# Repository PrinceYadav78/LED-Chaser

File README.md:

Designined in KiCAD, and FreeCAD

### Schematic

### PCB

### bom.csv

### Cart

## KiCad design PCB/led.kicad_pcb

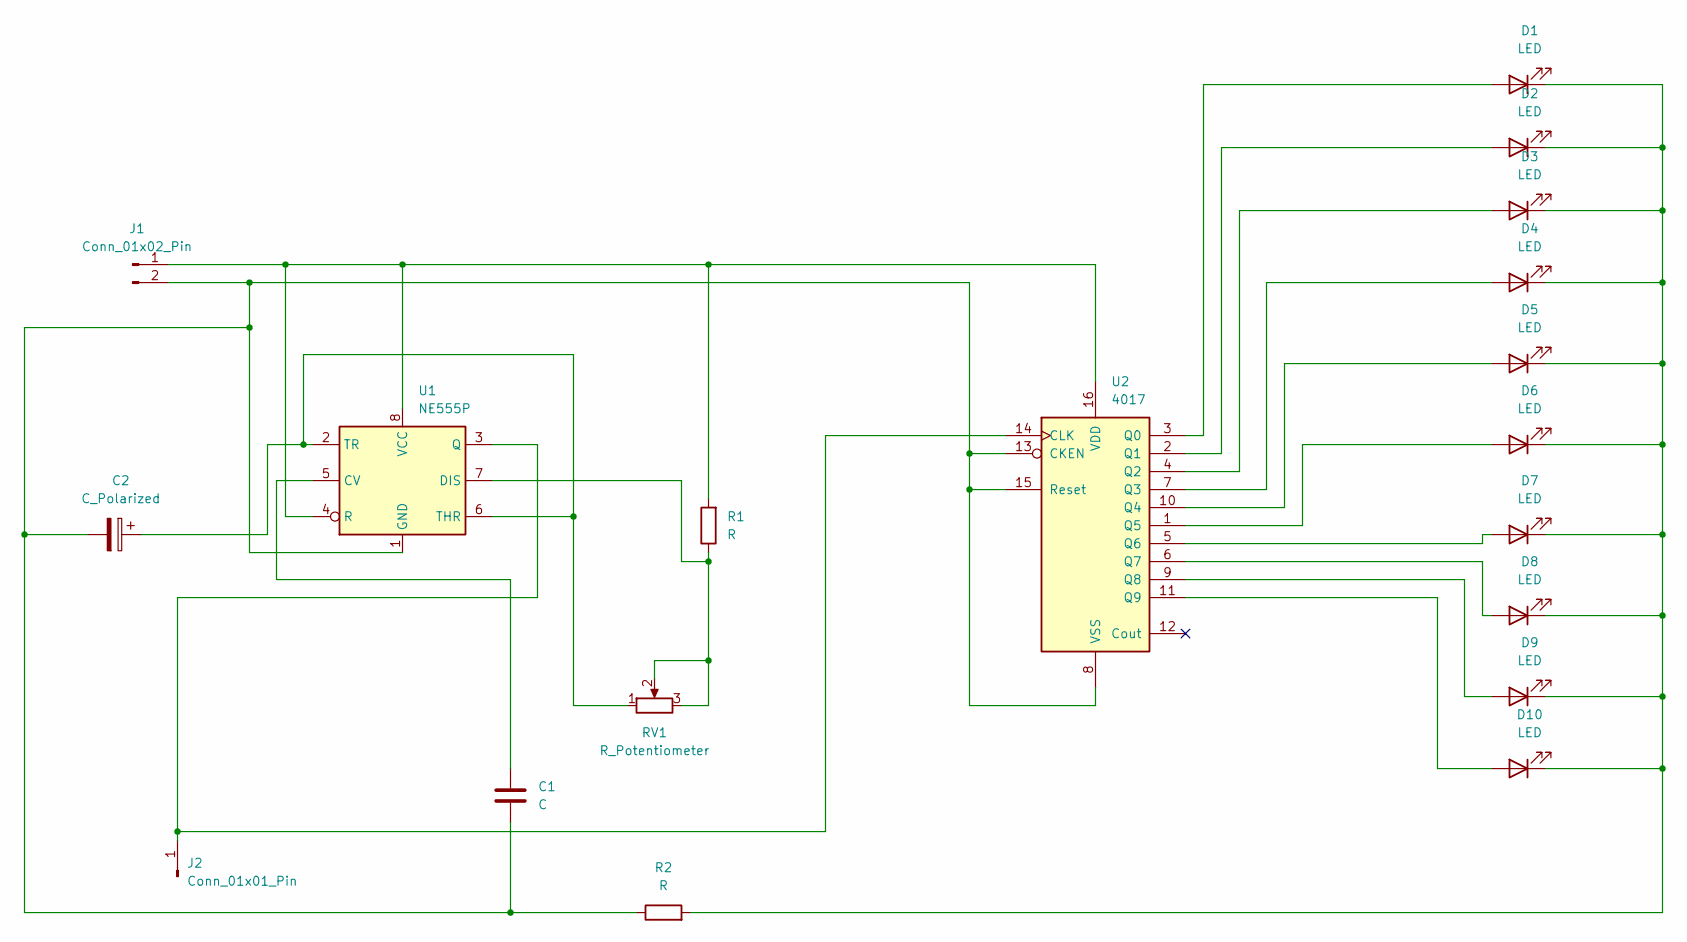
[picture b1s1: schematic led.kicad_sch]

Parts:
C1: C; C_Disc_D5.0mm_W2.5mm_P5.00mm
C2: C_Polarized; CP_Radial_D5.0mm_P2.50mm
D1, D2, D3, D4, D5, D6, D7, D8, D9, D10: LED; LED_D5.0mm
J1: Conn_01x02_Pin; PinHeader_1x02_P2.54mm_Vertical
J2: Conn_01x01_Pin; PinHeader_1x01_P2.54mm_Vertical
R1, R2: R; R_Axial_DIN0207_L6.3mm_D2.5mm_P7.62mm_Horizontal
RV1: R_Potentiometer; TRIM_3362P-1-103LF
U1: NE555P; DIP-8_W7.62mm
U2: 4017; DIP-16_W7.62mm

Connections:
unnamed: D1.2 (A), U2.3 (Q0)
unnamed: D1.1 (K), D2.1 (K), D3.1 (K), D4.1 (K), D5.1 (K), D6.1 (K), D7.1 (K), D8.1 (K), D9.1 (K), D10.1 (K), R2.2
unnamed: D2.2 (A), U2.2 (Q1)
unnamed: D3.2 (A), U2.4 (Q2)
unnamed: D4.2 (A), U2.7 (Q3)
unnamed: D5.2 (A), U2.10 (Q4)
unnamed: D6.2 (A), U2.1 (Q5)
unnamed: D7.2 (A), U2.5 (Q6)
unnamed: D8.2 (A), U2.6 (Q7)
unnamed: D9.2 (A), U2.9 (Q8)
unnamed: D10.2 (A), U2.11 (Q9)
unnamed: J1.1, R1.2, U1.4 (R), U1.8 (VCC), U2.16 (VDD)
unnamed: C1.2, C2.2, J1.2, R2.1, U1.1 (GND), U2.8 (VSS), U2.13 (CKEN), U2.15 (Reset)
unnamed: J2.1, U1.3 (Q), U2.14 (CLK)
unnamed: C1.1, U1.5 (CV)
unnamed: R1.1, RV1.2, RV1.3, U1.7 (DIS)
unnamed: C2.1, RV1.1, U1.2 (TR), U1.6 (THR)

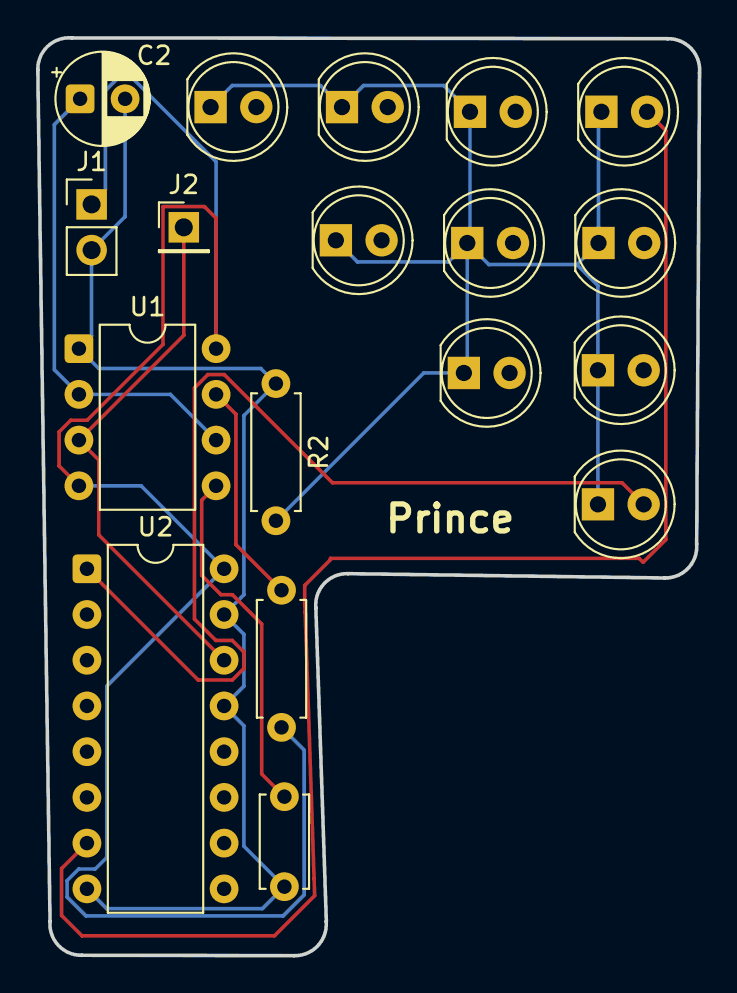
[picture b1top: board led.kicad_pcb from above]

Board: 4 copper layers, 36.8 x 51.0 mm, 18 parts (0 on the bottom side), 17 nets.

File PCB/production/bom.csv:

Designator,Footprint,Quantity,Value,LCSC Part #
C1,C_Disc_D5.0mm_W2.5mm_P5.00mm,1,C,
C2,CP_Radial_D5.0mm_P2.50mm,1,C_Polarized,
"D1, D10, D2, D3, D4, D5, D6, D7, D8, D9",LED_D5.0mm,10,LED,
J1,PinHeader_1x02_P2.54mm_Vertical,1,Conn_01x02_Pin,
J2,PinHeader_1x01_P2.54mm_Vertical,1,Conn_01x01_Pin,
"R1, R2",R_Axial_DIN0207_L6.3mm_D2.5mm_P7.62mm_Horizontal,2,R,
U1,DIP-8_W7.62mm,1,NE555P,
U2,DIP-16_W7.62mm,1,4017,
